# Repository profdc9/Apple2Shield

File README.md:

# Apple II Arduino Shield

This is a simple card to interface an Apple II bus to an Arduino Uno or an Arduino Shield using the 82C55 interface.  If stackable headers are soldered into the interface card, an Arduino Uno may be mounted on the back of the card, and shields may be stacked on the front of the card.  This way an Arduino Shield may be used without an Arduino by the card by bit-banging it with the 82C55, or an Arduino may control the card.  There is also a ROM on the board that can contain your own firmware if you desire, and the hardware to flash it.  The design is derived from another project http://www.github.com/profdc9/Apple2Card

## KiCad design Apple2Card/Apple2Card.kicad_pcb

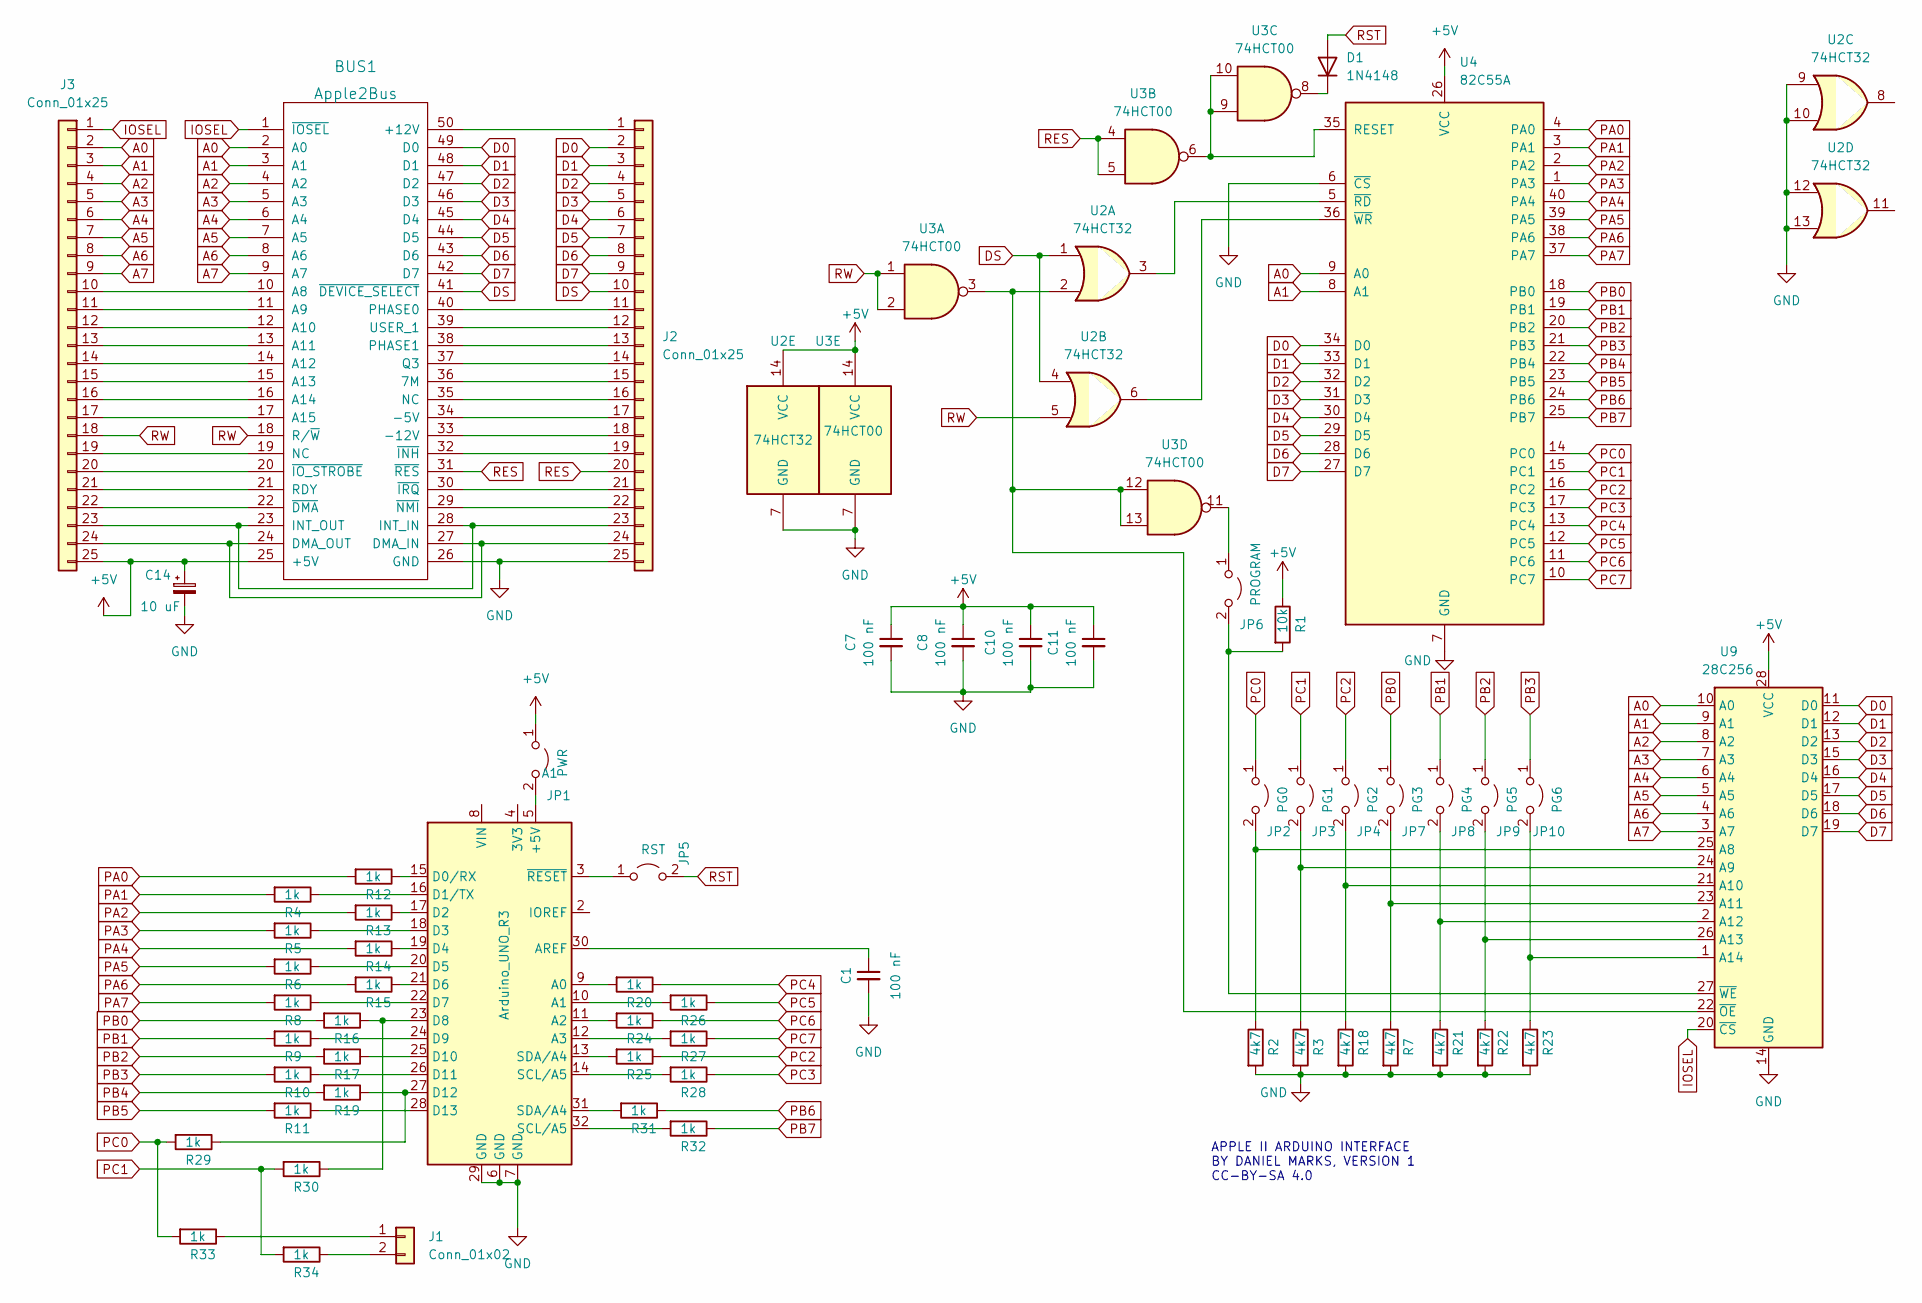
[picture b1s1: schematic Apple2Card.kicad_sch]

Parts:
A1: Arduino_UNO_R3
BUS1: Apple2Bus; Apple2Slot
C1, C7, C8, C10, C11: 100 nF; C_Disc_D5.0mm_W2.5mm_P5.00mm
C14: 10 uF; CP_Radial_D5.0mm_P2.50mm
D1: 1N4148; D_DO-35_SOD27_P7.62mm_Horizontal
J1: Conn_01x02; PinSocket_1x02_P2.54mm_Vertical
J2, J3: Conn_01x25; PinHeader_1x25_P2.54mm_Vertical
JP1: PWR; PinHeader_1x02_P2.54mm_Vertical
JP2: PG0; PinHeader_1x02_P2.54mm_Vertical
JP3: PG1; PinHeader_1x02_P2.54mm_Vertical
JP4: PG2; PinHeader_1x02_P2.54mm_Vertical
JP5: RST; PinHeader_1x02_P2.54mm_Vertical
JP6: PROGRAM; PinHeader_1x02_P2.54mm_Vertical
JP7: PG3; PinHeader_1x02_P2.54mm_Vertical
JP8: PG4; PinHeader_1x02_P2.54mm_Vertical
JP9: PG5; PinHeader_1x02_P2.54mm_Vertical
JP10: PG6; PinHeader_1x02_P2.54mm_Vertical
R1: 10k; R_Axial_DIN0207_L6.3mm_D2.5mm_P7.62mm_Horizontal
R2, R3, R7, R18, R21, R22, R23: 4k7; R_Axial_DIN0207_L6.3mm_D2.5mm_P7.62mm_Horizontal
R4, R5, R6, R8, R9, R10, R11, R12, R13, R14, R15, R16, R17, R19, R20, R24, R25, R26, R27, R28, R29, R30, R31, R32, R33, R34: 1k; R_Axial_DIN0207_L6.3mm_D2.5mm_P7.62mm_Horizontal
U2: 74HCT32; DIP-14_W7.62mm_Socket
U3: 74HCT00; DIP-14_W7.62mm_Socket
U4: 82C55A; DIP-40_W15.24mm_Socket
U9: 28C256; DIP-28_W15.24mm_Socket

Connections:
+5V: BUS1.25 (+5V), C7.1, C8.1, C10.1, C11.1, C14.1, J3.25, JP1.1 (A), R1.1, U2.14 (VCC), U3.14 (VCC), U4.26 (VCC), U9.28 (VCC)
A0: BUS1.2 (A0), J3.2, U4.9 (A0), U9.10 (A0)
A1: BUS1.3 (A1), J3.3, U4.8 (A1), U9.9 (A1)
A2: BUS1.4 (A2), J3.4, U9.8 (A2)
A3: BUS1.5 (A3), J3.5, U9.7 (A3)
A4: BUS1.6 (A4), J3.6, U9.6 (A4)
A5: BUS1.7 (A5), J3.7, U9.5 (A5)
A6: BUS1.8 (A6), J3.8, U9.4 (A6)
A7: BUS1.9 (A7), J3.9, U9.3 (A7)
D0: BUS1.49 (D0), J2.2, U4.34 (D0), U9.11 (D0)
D1: BUS1.48 (D1), J2.3, U4.33 (D1), U9.12 (D1)
D2: BUS1.47 (D2), J2.4, U4.32 (D2), U9.13 (D2)
D3: BUS1.46 (D3), J2.5, U4.31 (D3), U9.15 (D3)
D4: BUS1.45 (D4), J2.6, U4.30 (D4), U9.16 (D4)
D5: BUS1.44 (D5), J2.7, U4.29 (D5), U9.17 (D5)
D6: BUS1.43 (D6), J2.8, U4.28 (D6), U9.18 (D6)
D7: BUS1.42 (D7), J2.9, U4.27 (D7), U9.19 (D7)
DS: BUS1.41 (~DEVICE_SELECT), J2.10, U2.1, U2.4
GND: A1.6 (GND), A1.7 (GND), A1.29 (GND), BUS1.26 (GND), C1.2, C7.2, C8.2, C10.2, C11.2, C14.2, J2.25, R2.2, R3.2, R7.2, R18.2, R21.2, R22.2, R23.2, U2.7 (GND), U2.9, U2.10, U2.12, U2.13, U3.7 (GND), U4.6 (~CS), U4.7 (GND), U9.14 (GND)
IOSEL: BUS1.1 (~IOSEL), J3.1, U9.20 (~CS)
unnamed: A1.3 (~RESET), JP5.1 (A)
unnamed: A1.5 (+5V), JP1.2 (B)
unnamed: A1.9 (A0), R20.2
unnamed: A1.10 (A1), R26.2
unnamed: A1.11 (A2), R24.2
unnamed: A1.12 (A3), R27.2
unnamed: A1.13 (SDA/A4), R25.2
unnamed: A1.14 (SCL/A5), R28.2
unnamed: A1.15 (D0/RX), R12.1
unnamed: A1.16 (D1/TX), R4.1
unnamed: A1.17 (D2), R13.1
unnamed: A1.18 (D3), R5.1
unnamed: A1.19 (D4), R14.1
unnamed: A1.20 (D5), R6.1
unnamed: A1.21 (D6), R15.1
unnamed: A1.22 (D7), R8.1
unnamed: A1.23 (D8), R16.1, R30.1
unnamed: A1.24 (D9), R9.1
unnamed: A1.25 (D10), R17.1
unnamed: A1.26 (D11), R10.1
unnamed: A1.27 (D12), R19.1, R29.1
unnamed: A1.28 (D13), R11.1
unnamed: A1.30 (AREF), C1.1
unnamed: A1.31 (SDA/A4), R31.2
unnamed: A1.32 (SCL/A5), R32.2
unnamed: BUS1.10 (A8), J3.10
unnamed: BUS1.11 (A9), J3.11
unnamed: BUS1.12 (A10), J3.12
unnamed: BUS1.13 (A11), J3.13
unnamed: BUS1.14 (A12), J3.14
unnamed: BUS1.15 (A13), J3.15
unnamed: BUS1.16 (A14), J3.16
unnamed: BUS1.17 (A15), J3.17
unnamed: BUS1.19 (NC), J3.19
unnamed: BUS1.20 (~IO_STROBE), J3.20
unnamed: BUS1.21 (RDY), J3.21
unnamed: BUS1.22 (~DMA), J3.22
unnamed: BUS1.23 (INT_OUT), BUS1.28 (INT_IN), J2.23, J3.23
unnamed: BUS1.24 (DMA_OUT), BUS1.27 (DMA_IN), J2.24, J3.24
unnamed: BUS1.29 (~NMI), J2.22
unnamed: BUS1.30 (~IRQ), J2.21
unnamed: BUS1.32 (~INH), J2.19
unnamed: BUS1.33 (-12V), J2.18
unnamed: BUS1.34 (-5V), J2.17
unnamed: BUS1.35 (NC), J2.16
unnamed: BUS1.36 (7M), J2.15
unnamed: BUS1.37 (Q3), J2.14
unnamed: BUS1.38 (PHASE1), J2.13
unnamed: BUS1.39 (USER_1), J2.12
unnamed: BUS1.40 (PHASE0), J2.11
unnamed: BUS1.50 (+12V), J2.1
unnamed: D1.1 (K), U3.8
unnamed: J1.1, R33.1
unnamed: J1.2, R34.1
unnamed: JP2.2 (B), R2.1, U9.25 (A8)
unnamed: JP3.2 (B), R3.1, U9.24 (A9)
unnamed: JP4.2 (B), R18.1, U9.21 (A10)
unnamed: JP6.1 (A), U3.11
unnamed: JP6.2 (B), R1.2, U9.27 (~WE)
unnamed: JP7.2 (B), R7.1, U9.23 (A11)
unnamed: JP8.2 (B), R21.1, U9.2 (A12)
unnamed: JP9.2 (B), R22.1, U9.26 (A13)
unnamed: JP10.2 (B), R23.1, U9.1 (A14)
unnamed: U2.2, U3.3, U3.12, U3.13, U9.22 (~OE)
unnamed: U2.3, U4.5 (~RD)
unnamed: U2.6, U4.36 (~WR)
unnamed: U3.6, U3.9, U3.10, U4.35 (RESET)
PA0: R12.2, U4.4 (PA0)
PA1: R4.2, U4.3 (PA1)
PA2: R13.2, U4.2 (PA2)
PA3: R5.2, U4.1 (PA3)
PA4: R14.2, U4.40 (PA4)
PA5: R6.2, U4.39 (PA5)
PA6: R15.2, U4.38 (PA6)
PA7: R8.2, U4.37 (PA7)
PB0: JP7.1 (A), R16.2, U4.18 (PB0)
PB1: JP8.1 (A), R9.2, U4.19 (PB1)
PB2: JP9.1 (A), R17.2, U4.20 (PB2)
PB3: JP10.1 (A), R10.2, U4.21 (PB3)
PB4: R19.2, U4.22 (PB4)
PB5: R11.2, U4.23 (PB5)
PB6: R31.1, U4.24 (PB6)
PB7: R32.1, U4.25 (PB7)
PC0: JP2.1 (A), R29.2, R33.2, U4.14 (PC0)
PC1: JP3.1 (A), R30.2, R34.2, U4.15 (PC1)
PC2: JP4.1 (A), R25.1, U4.16 (PC2)
PC3: R28.1, U4.17 (PC3)
PC4: R20.1, U4.13 (PC4)
PC5: R26.1, U4.12 (PC5)
PC6: R24.1, U4.11 (PC6)
PC7: R27.1, U4.10 (PC7)
RES: BUS1.31 (~RES), J2.20, U3.4, U3.5
RST: D1.2 (A), JP5.2 (B)
RW: BUS1.18 (R/~W), J3.18, U2.5, U3.1, U3.2

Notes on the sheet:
APPLE II ARDUINO INTERFACE BY DANIEL MARKS, VERSION 1 CC-BY-SA 4.0

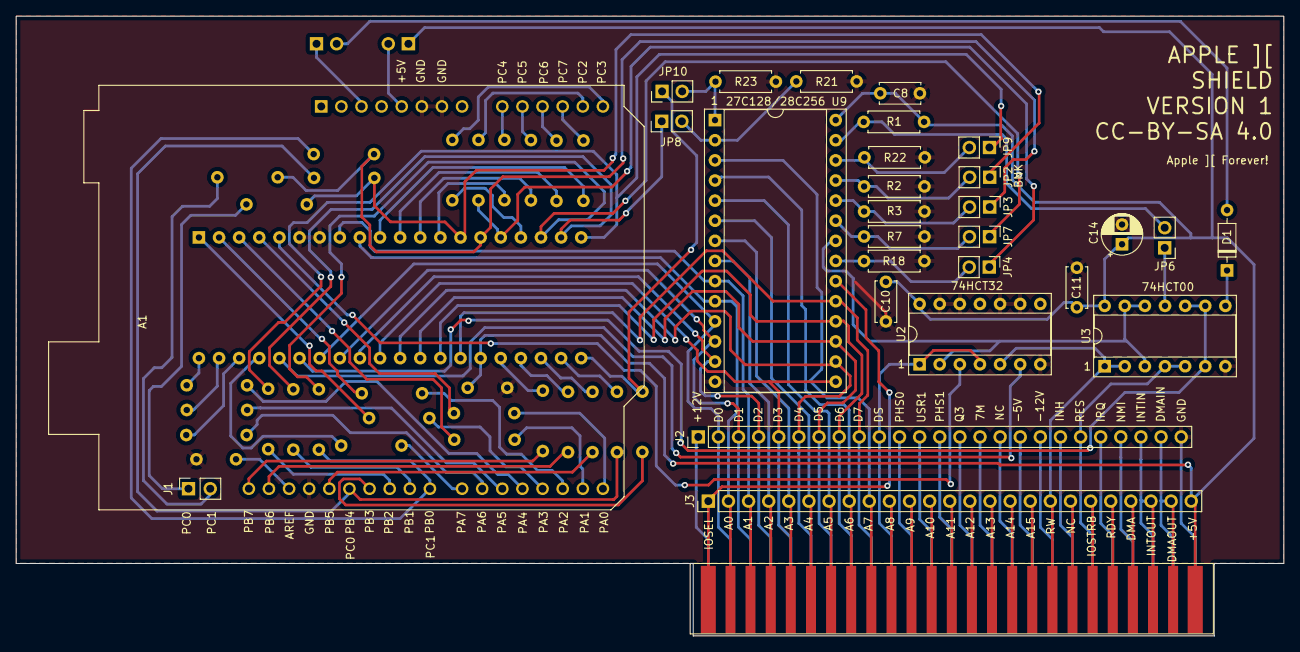
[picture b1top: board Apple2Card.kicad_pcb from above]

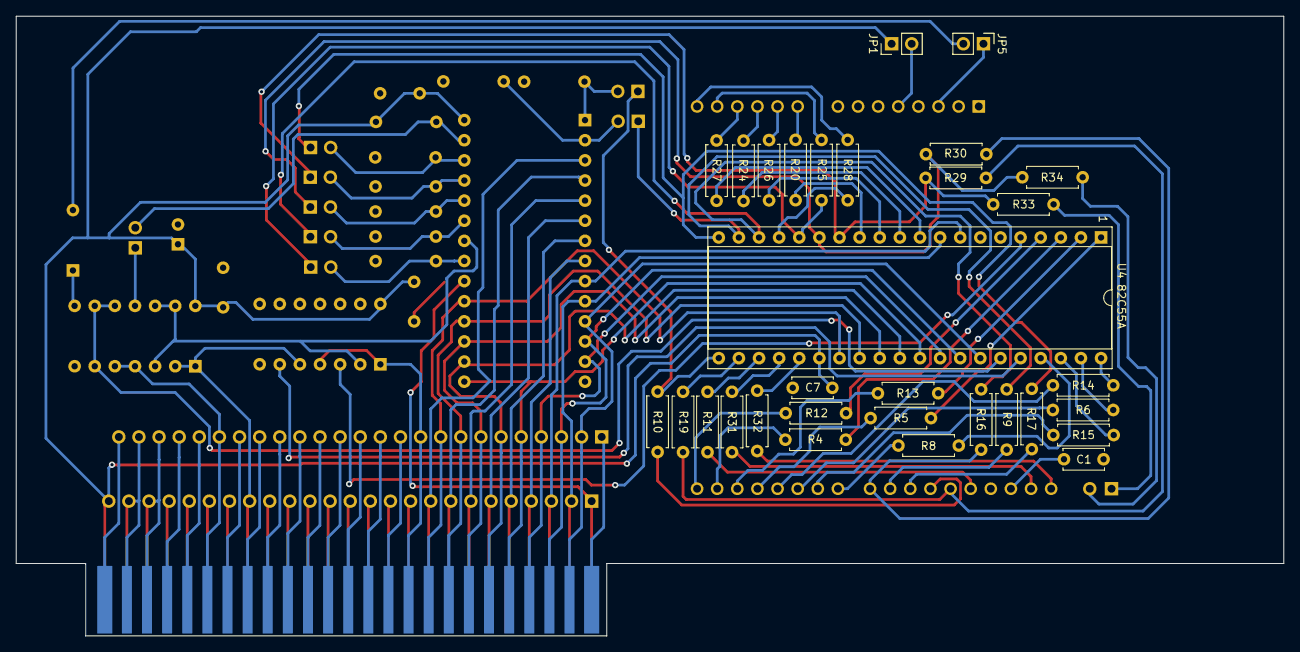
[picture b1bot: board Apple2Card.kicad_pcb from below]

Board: 2 copper layers, 160.0 x 78.2 mm, 60 parts (31 on the bottom side), 114 nets.

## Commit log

2022-06-15 JLCPCB Order 2022-06-15
2022-07-02 Fixed layout a bit, added pictures
